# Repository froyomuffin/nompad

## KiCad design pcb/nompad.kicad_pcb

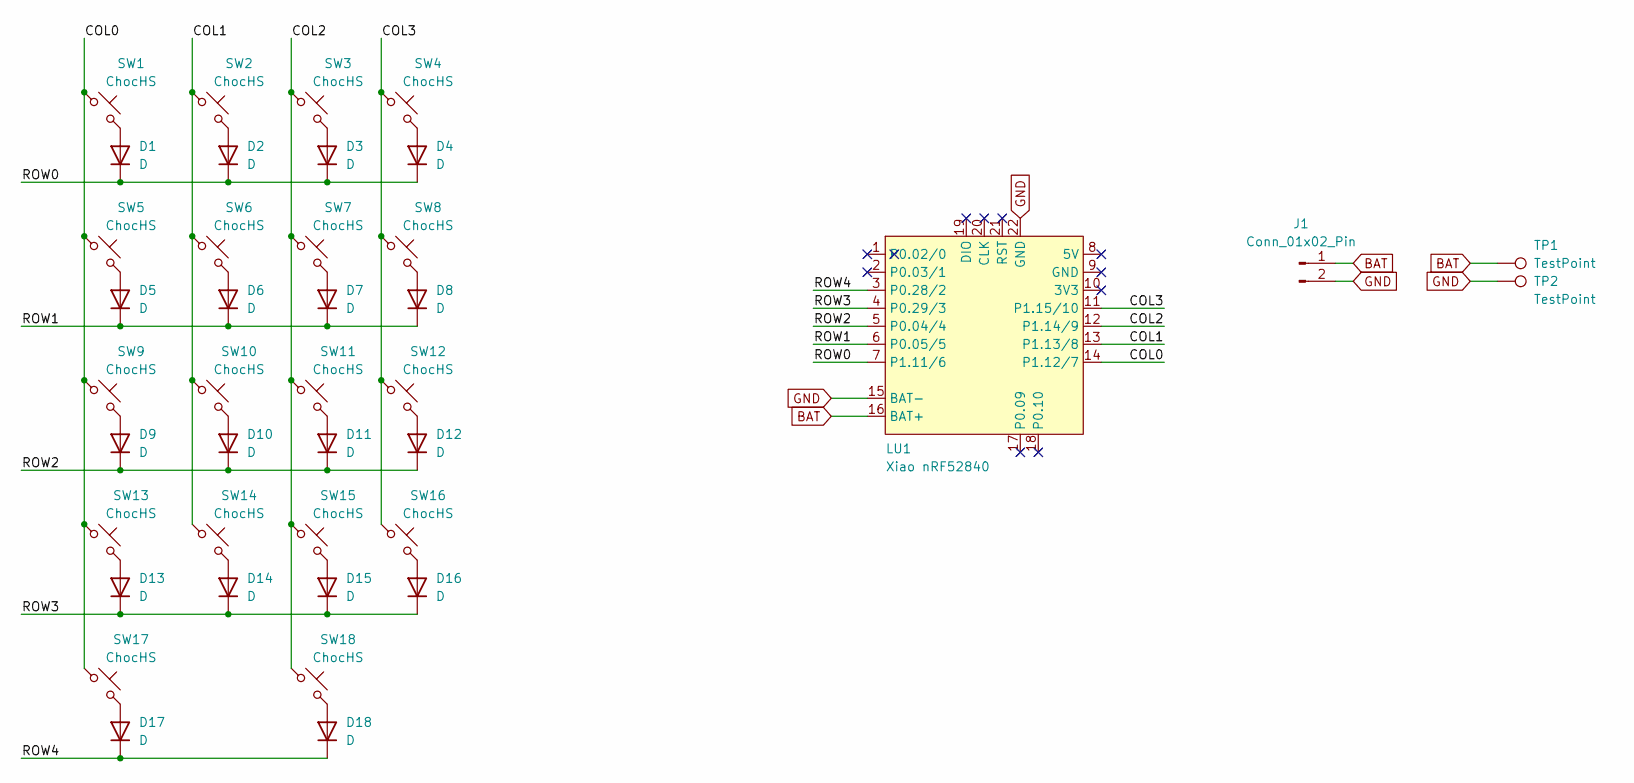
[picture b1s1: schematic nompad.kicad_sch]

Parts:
D1, D2, D3, D4, D5, D6, D7, D8, D9, D10, D11, D12, D13, D14, D15, D16, D17, D18: D; Diode_SOD123
J1: Conn_01x02_Pin; JST_ACH_BM02B-ACHSS-GAN-ETF_1x02-1MP_P1.20mm_Vertical
LU1: Xiao nRF52840; xiao-ble-smd-cutout-aternate
SW1, SW2, SW3, SW4, SW5, SW6, SW7, SW8, SW9, SW10, SW11, SW12, SW13, SW14, SW15, SW16, SW17, SW18: ChocHS; Kailh_PG1350_1353_Combo_No_Socket
TP1, TP2: TestPoint; TestPoint_Pad_D2.0mm

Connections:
/COL0: LU1.14 (P1.12/7), SW1.1, SW5.1, SW9.1, SW13.1, SW17.1
/COL1: LU1.13 (P1.13/8), SW2.1, SW6.1, SW10.1, SW14.1
/COL2: LU1.12 (P1.14/9), SW3.1, SW7.1, SW11.1, SW15.1, SW18.1
/COL3: LU1.11 (P1.15/10), SW4.1, SW8.1, SW12.1, SW16.1
/ROW0: D1.1 (K), D2.1 (K), D3.1 (K), D4.1 (K), LU1.7 (P1.11/6)
/ROW1: D5.1 (K), D6.1 (K), D7.1 (K), D8.1 (K), LU1.6 (P0.05/5)
/ROW2: D9.1 (K), D10.1 (K), D11.1 (K), D12.1 (K), LU1.5 (P0.04/4)
/ROW3: D13.1 (K), D14.1 (K), D15.1 (K), D16.1 (K), LU1.4 (P0.29/3)
/ROW4: D17.1 (K), D18.1 (K), LU1.3 (P0.28/2)
BAT: J1.1, LU1.16 (BAT+), TP1.1
GND: J1.2, LU1.15 (BAT-), LU1.22 (GND), TP2.1
unnamed: D1.2 (A), SW1.2
unnamed: D2.2 (A), SW2.2
unnamed: D3.2 (A), SW3.2
unnamed: D4.2 (A), SW4.2
unnamed: D5.2 (A), SW5.2
unnamed: D6.2 (A), SW6.2
unnamed: D7.2 (A), SW7.2
unnamed: D8.2 (A), SW8.2
unnamed: D9.2 (A), SW9.2
unnamed: D10.2 (A), SW10.2
unnamed: D11.2 (A), SW11.2
unnamed: D12.2 (A), SW12.2
unnamed: D13.2 (A), SW13.2
unnamed: D14.2 (A), SW14.2
unnamed: D15.2 (A), SW15.2
unnamed: D16.2 (A), SW16.2
unnamed: D17.2 (A), SW17.2
unnamed: D18.2 (A), SW18.2

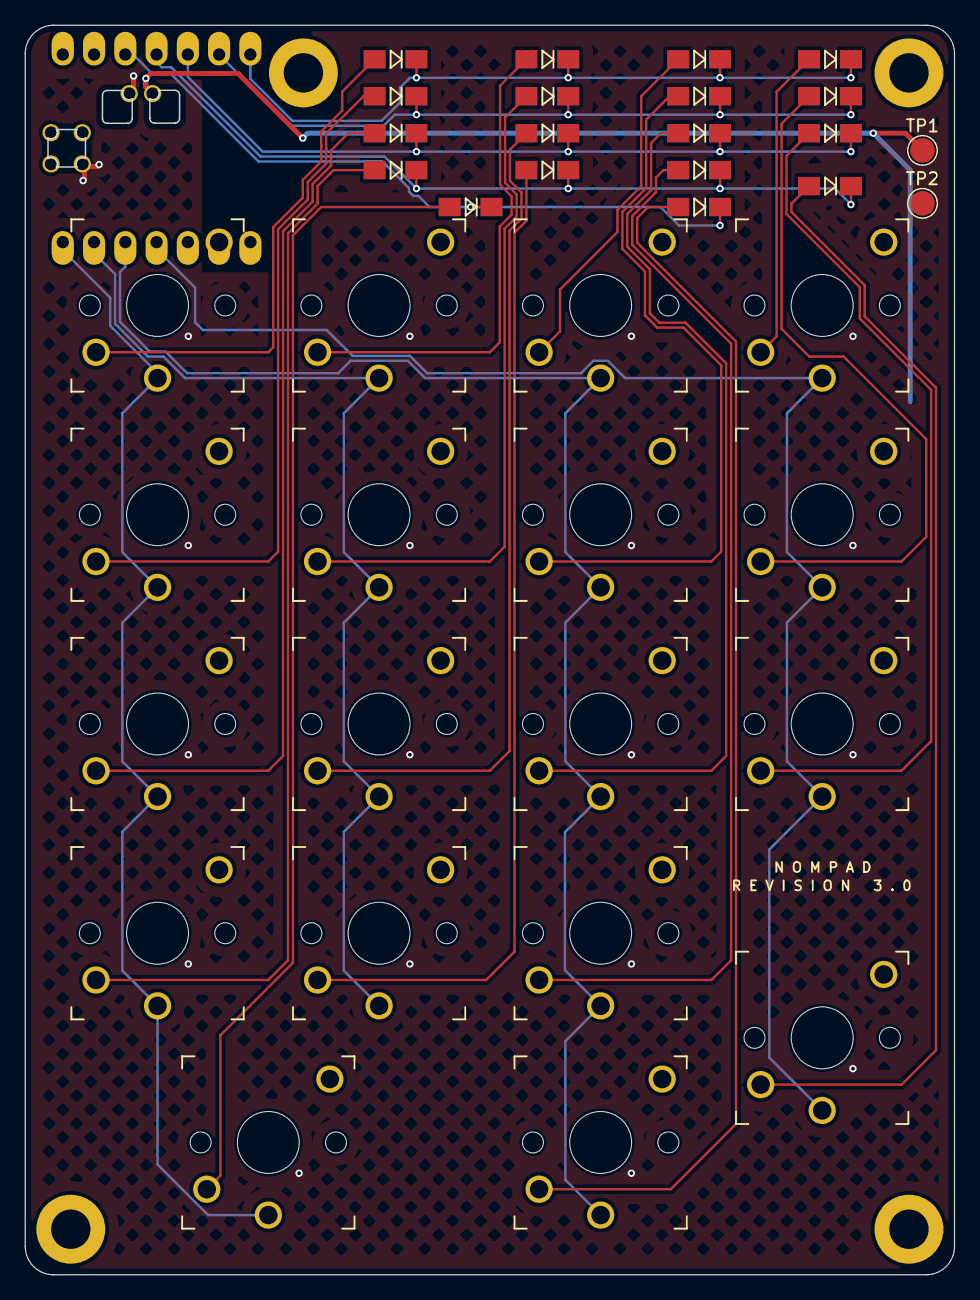
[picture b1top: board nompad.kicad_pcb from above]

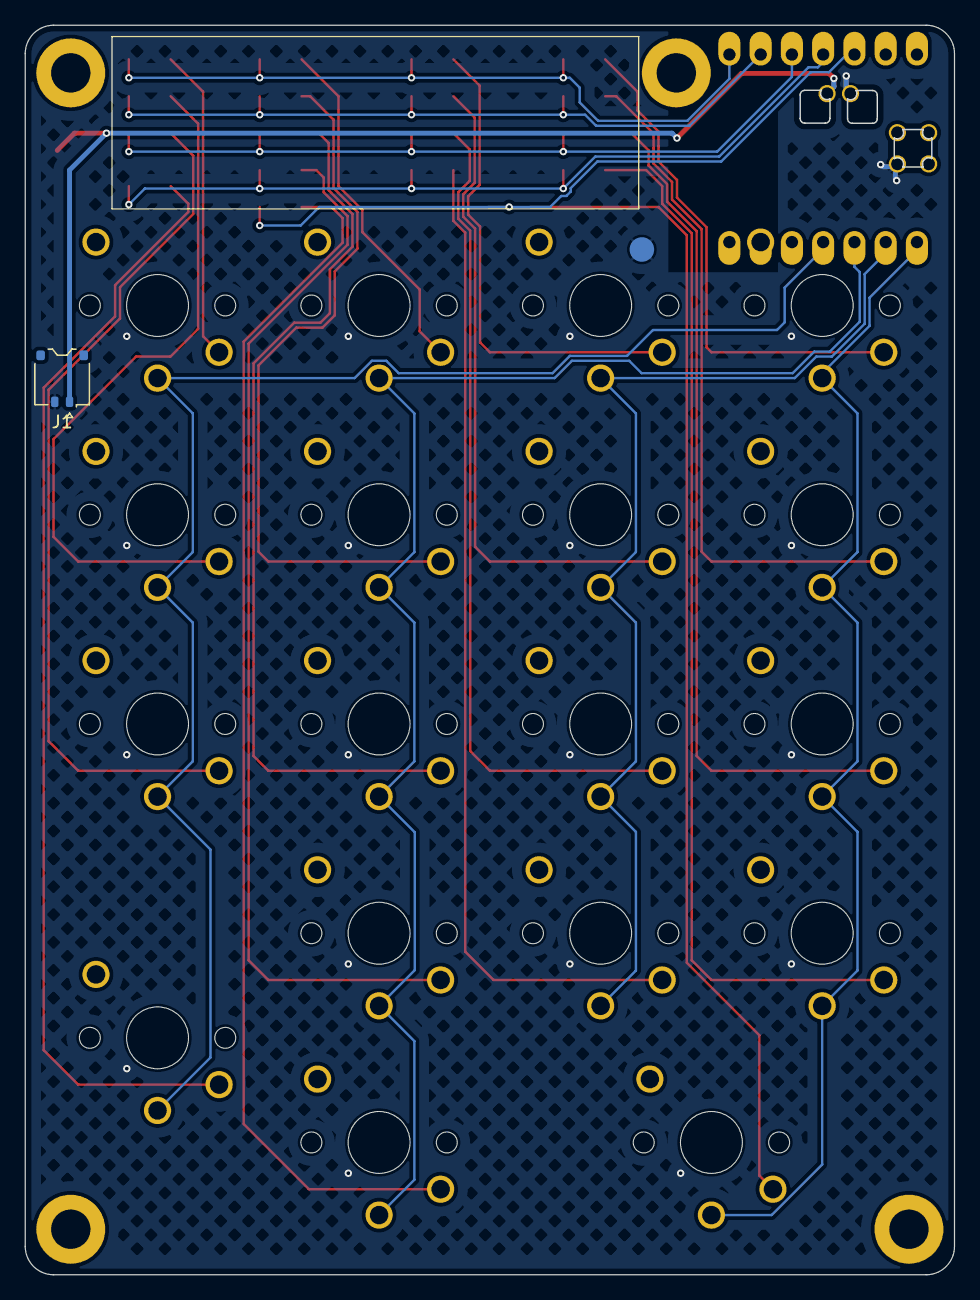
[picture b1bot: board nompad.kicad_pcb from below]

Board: 2 copper layers, 75.5 x 101.5 mm, 40 parts (2 on the bottom side), 29 nets.

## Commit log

2025-05-28 Add gitignore
2025-05-28 First Version
2025-05-28 Move one of the screw sockets under case
2025-05-28 Cleanup
2025-05-28 Center everything
2025-05-28 Align socket
2025-05-29 Shrink PCB
